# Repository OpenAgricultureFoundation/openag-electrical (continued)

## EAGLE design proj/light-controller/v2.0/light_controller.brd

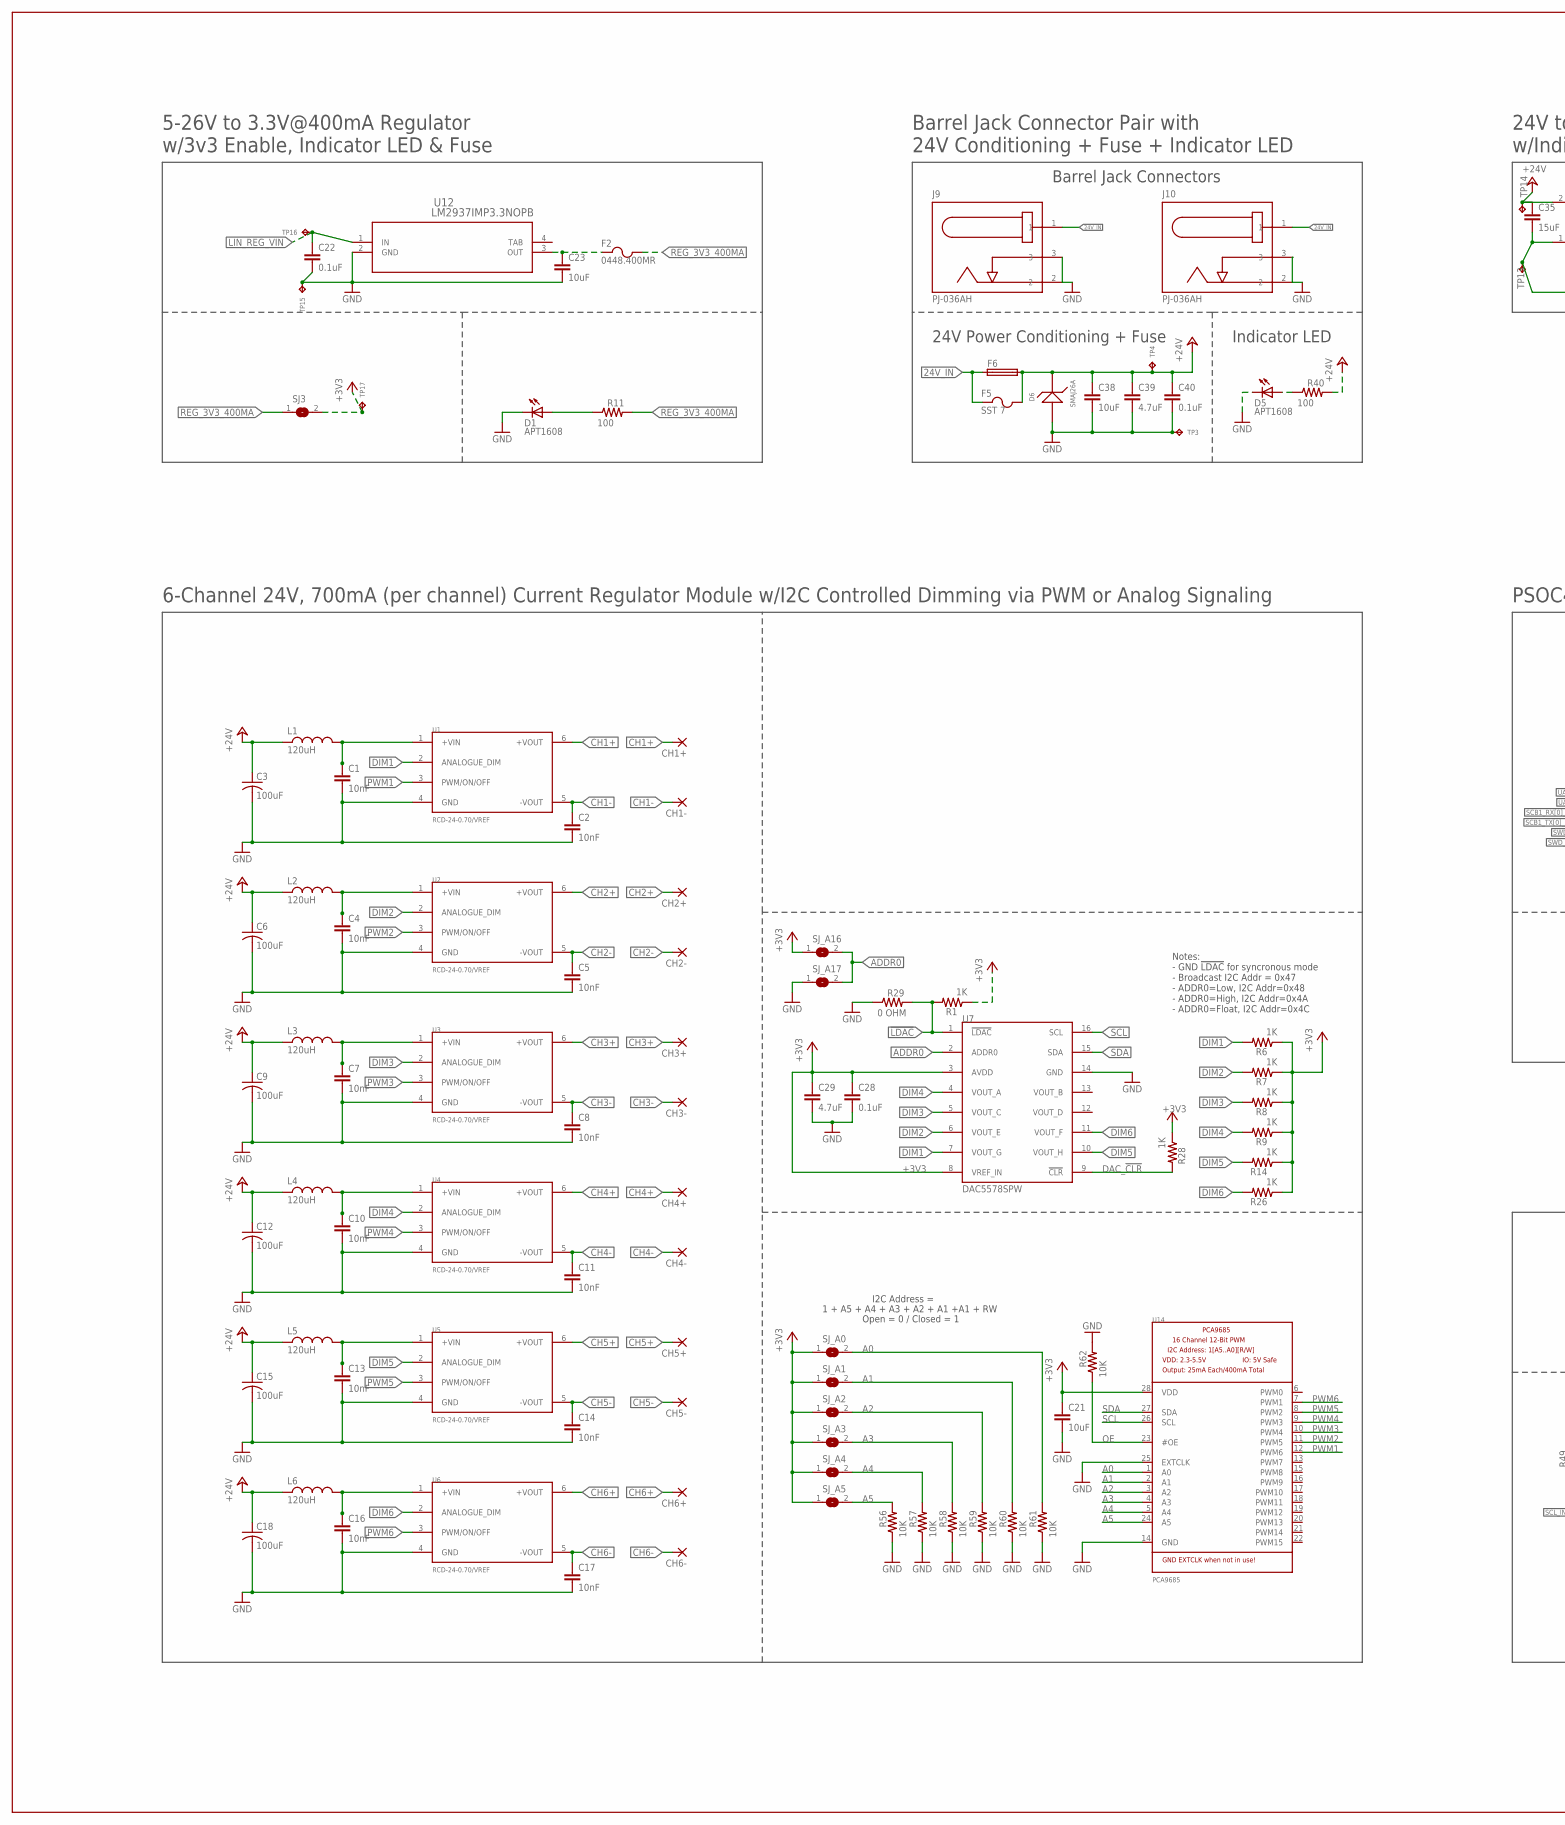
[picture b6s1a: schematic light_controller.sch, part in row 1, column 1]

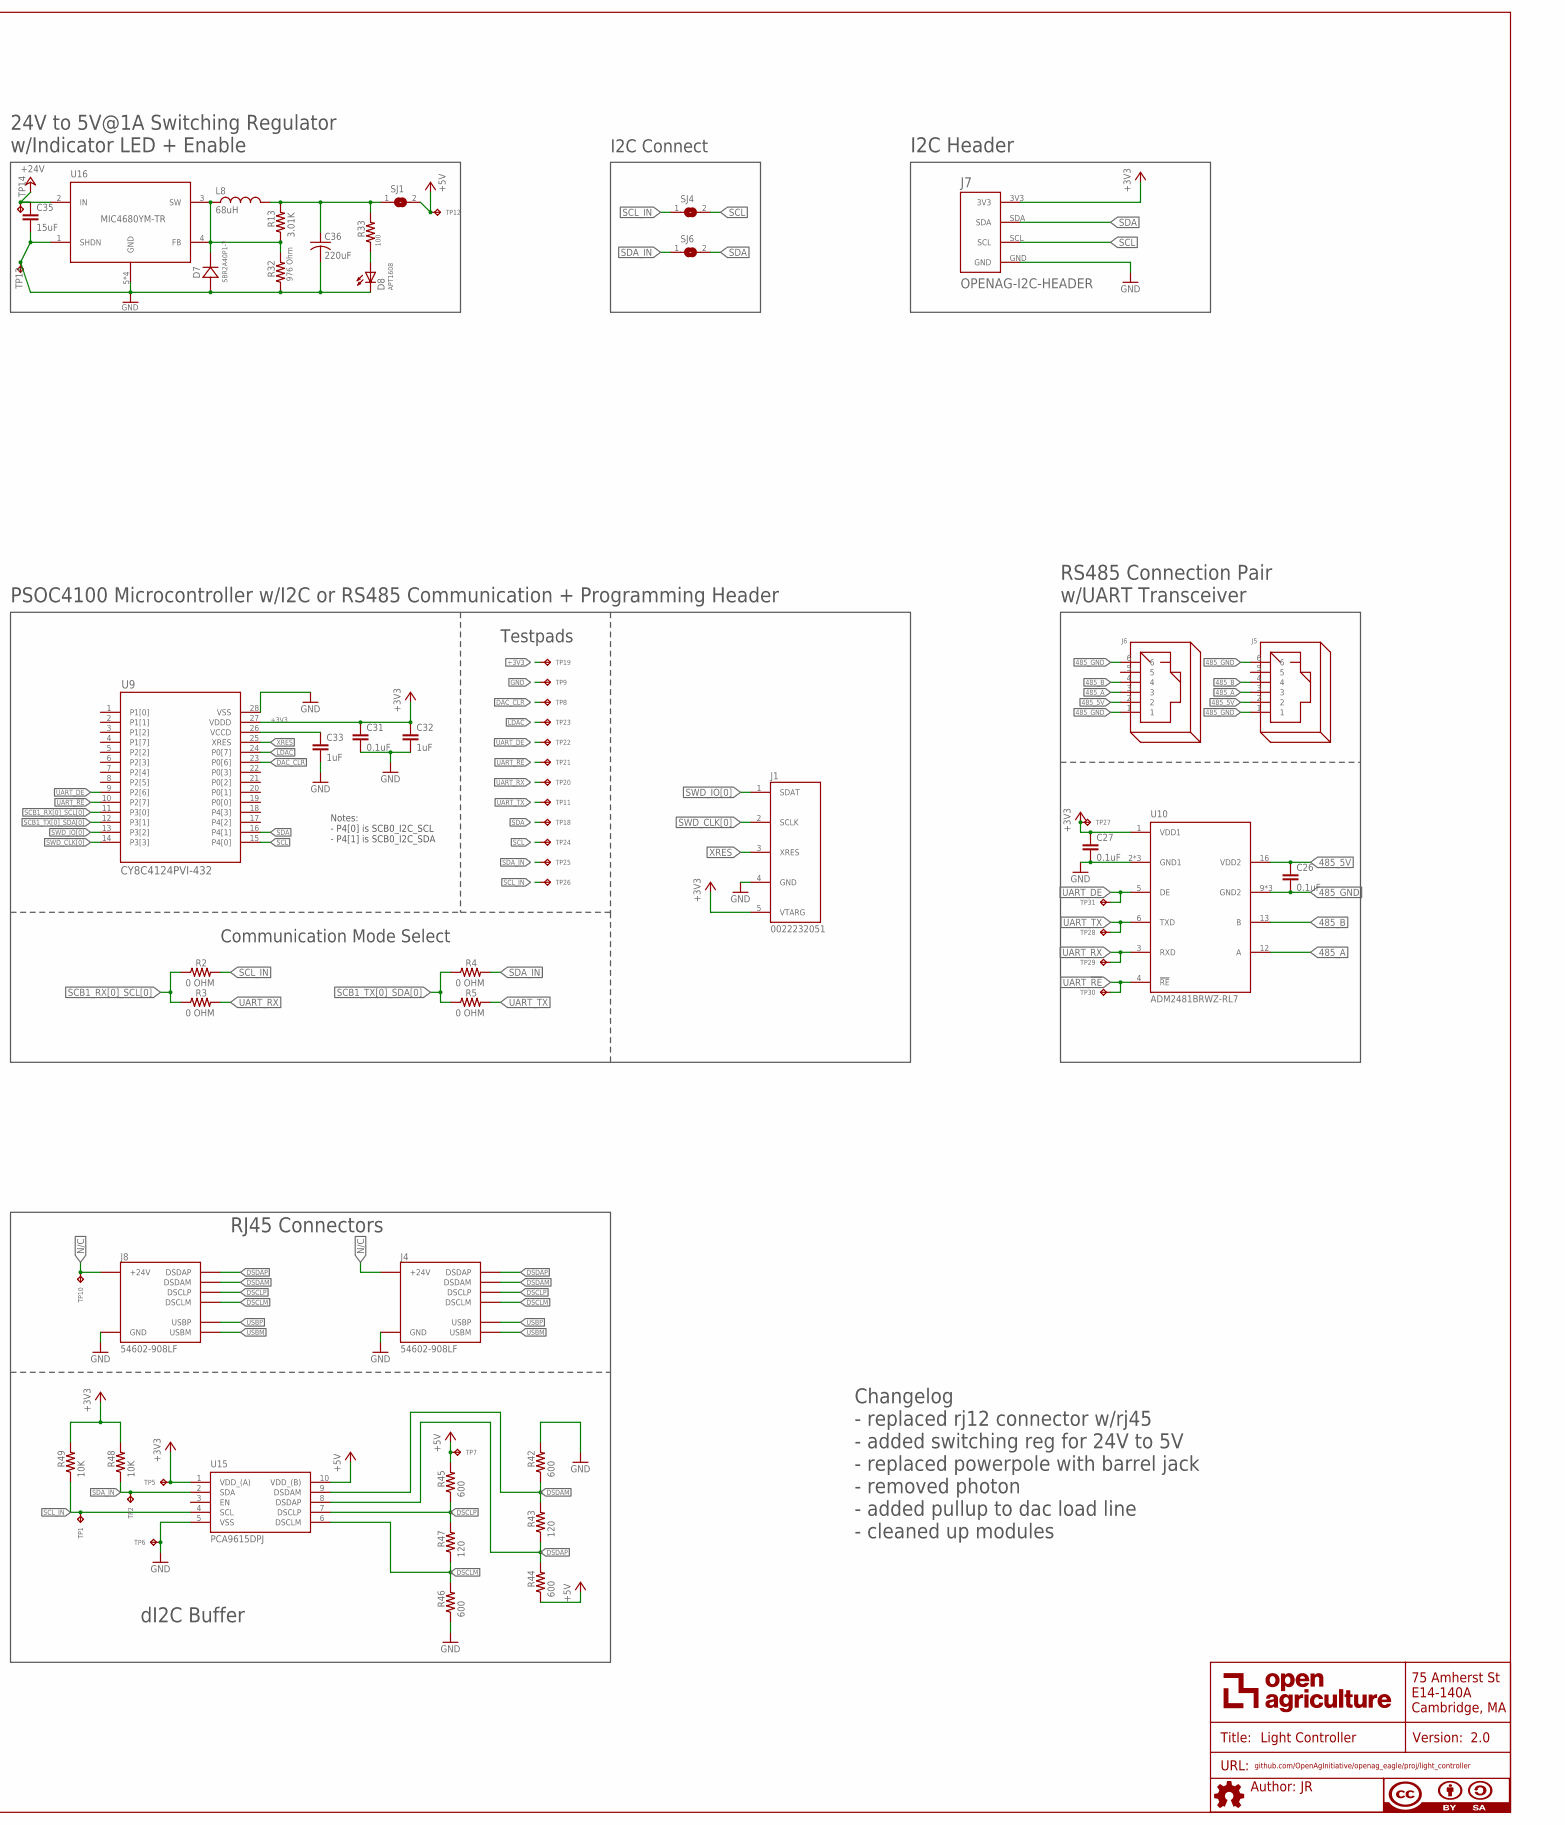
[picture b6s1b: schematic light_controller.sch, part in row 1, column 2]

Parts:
C1, C2, C4, C5, C7, C8, C10, C11, C13, C14, C16, C17: 10nF; C0603
C3, C6, C9, C12, C15, C18: 100uF; EEE-1HA101UP
C21, C23, C38: 10uF; C0805
C22, C26, C27, C28, C31, C40: 0.1uF; C0603
C29, C39: 4.7uF; C0805
C32, C33: 1uF; C0603
C35: 15uF; C0805
C36: 220uF; CT7343
CH1+, CH1-, CH2+, CH2-, CH3+, CH3-, CH4+, CH4-, CH5+, CH5-, CH6+, CH6-: 3,17/1,3
D1, D5, D8: APT1608; CHIPLED_0603
D6: SMAJ26A; SMA
D7: SBR2A40P1-7; POWERDI123
F2: 0448.400MR; 0603
F5: SST 7; SS
F6: GSH15
FRAME1: DOCFIELD
J1: 0022232051; 22-23-2051
J4, J8: 54602-908LF; OPENAG-V1-RJ45
J5, J6: OPENAG-RS485-RJ12
J7: OPENAG-I2C-HEADER
J9, J10: PJ-036AH
L1, L2, L3, L4, L5, L6: 120uH; 74404064121
L8: 68uH; UP2B
R1, R6, R7, R8, R9, R14, R26, R28: 1K; RC0603N
R2, R3, R4, R5, R29: 0 OHM; RC0603N
R11, R33, R40: 100; RC0603N
R13: 3.01K; RC0603N
R32: 976 Ohm; RC0603N
R42, R44, R45, R46: 600; RC0603N
R43, R47: 120; RC0603N
R48, R49, R56, R57, R58, R59, R60, R61, R62: 10K; RC0603N
SJ1, SJ3, SJ4, SJ6: SOLDERJUMPERREFLOW_NOPASTE; SOLDERJUMPER_REFLOW_NOPASTE
SJ_A0, SJ_A1, SJ_A2, SJ_A3, SJ_A4, SJ_A5, SJ_A16, SJ_A17: SOLDERJUMPERREFLOW_NOPASTE; SOLDERJUMPER_REFLOW_NOPASTE
TP1, TP2, TP3, TP4, TP5, TP6, TP7, TP10, TP12, TP13, TP14, TP15, TP16, TP17: TPTP06R; TP06R
TP8, TP9, TP11, TP18, TP19, TP20, TP21, TP22, TP23, TP24, TP25, TP26, TP27, TP28, TP29, TP30, TP31: TPTP04R; TP04R
U1, U2, U3, U4, U5, U6: RCD-24-0.70/VREF; RCD-24-PINNED
U7: DAC5578SPW; TSSOP16
U9: CY8C4124PVI-432; SSOP-28
U10: ADM2481BRWZ-RL7; SOIC16LWB
U12: LM2937IMP3.3NOPB; MP04A
U14: PCA9685; TSSOP28
U15: PCA9615DPJ; SOP50P490X110-10N
U16: MIC4680YM-TR; SOIC8

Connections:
24V_IN: F5.1, F6.1, J9.1, J10.1
485_5V: C26.1, J5.2, J6.2, U10.16 (VDD2)
485_A: J5.3, J6.3, U10.12 (A)
485_B: J5.4, J6.4, U10.13 (B)
485_GND: C26.2, J5.1, J5.6, J6.1, J6.6, U10.9 (GND2), U10.10 (GND2), U10.15 (GND2)
!LDAC!: R1.2, R29.2, TP23.1, U7.1 (!LDAC!), U9.24 (P0[7])
+3V3: C21.1, C27.1, C28.1, C29.1, C31.1, C32.1, J1.5 (VTARG), J7.3V3, R1.1, R6.1, R7.1, R8.1, R9.1, R14.1, R26.1, R28.1, R48.2, R49.2, SJ3.2, SJ_A0.1, SJ_A1.1, SJ_A2.1, SJ_A3.1, SJ_A4.1, SJ_A5.1, SJ_A16.1, TP5.TP, TP17.TP, TP19.1, TP27.1, U7.3 (AVDD), U7.8 (VREF_IN), U9.27 (VDDD), U10.1 (VDD1), U14.28 (VDD), U15.1 (VDD_(A))
+5V: R44.1, R45.2, SJ1.2, TP7.TP, TP12.TP, U15.10 (VDD_(B))
+24V: C3.+ (1(+)), C6.+ (1(+)), C9.+ (1(+)), C12.+ (1(+)), C15.+ (1(+)), C18.+ (1(+)), C35.1, C38.1, C39.1, C40.1, D6.1, F5.2, F6.2, L1.1, L2.1, L3.1, L4.1, L5.1, L6.1, R40.2, TP4.TP, TP14.TP, U16.2 (IN)
A0: R61.2, SJ_A0.2, U14.1 (A0)
A1: R60.2, SJ_A1.2, U14.2 (A1)
A2: R59.2, SJ_A2.2, U14.3 (A2)
A3: R58.2, SJ_A3.2, U14.4 (A3)
A4: R57.2, SJ_A4.2, U14.5 (A4)
A5: R56.2, SJ_A5.2, U14.24 (A5)
ADDR0: SJ_A16.2, SJ_A17.2, U7.2 (ADDR0)
CH1+: CH1+.1, U1.6 (+VOUT)
CH1-: C2.1, CH1-.1, U1.5 (-VOUT)
CH2+: CH2+.1, U2.6 (+VOUT)
CH2-: C5.1, CH2-.1, U2.5 (-VOUT)
CH3+: CH3+.1, U3.6 (+VOUT)
CH3-: C8.1, CH3-.1, U3.5 (-VOUT)
CH4+: CH4+.1, U4.6 (+VOUT)
CH4-: C11.1, CH4-.1, U4.5 (-VOUT)
CH5+: CH5+.1, U5.6 (+VOUT)
CH5-: C14.1, CH5-.1, U5.5 (-VOUT)
CH6+: CH6+.1, U6.6 (+VOUT)
CH6-: C17.1, CH6-.1, U6.5 (-VOUT)
DAC_!CLR!: R28.2, TP8.1, U7.9 (!CLR!), U9.23 (P0[6])
DIM1: R6.2, U1.2 (ANALOGUE_DIM), U7.7 (VOUT_G)
DIM2: R7.2, U2.2 (ANALOGUE_DIM), U7.6 (VOUT_E)
DIM3: R8.2, U3.2 (ANALOGUE_DIM), U7.5 (VOUT_C)
DIM4: R9.2, U4.2 (ANALOGUE_DIM), U7.4 (VOUT_A)
DIM5: R14.2, U5.2 (ANALOGUE_DIM), U7.10 (VOUT_H)
DIM6: R26.2, U6.2 (ANALOGUE_DIM), U7.11 (VOUT_F)
DSCLM: J4.DSCLM(5) (DSCLM), J8.DSCLM(5) (DSCLM), R46.2, R47.1, U15.6 (DSCLM)
DSCLP: J4.DSCLP(4) (DSCLP), J8.DSCLP(4) (DSCLP), R45.1, R47.2, U15.7 (DSCLP)
DSDAM: J4.DSDAM(2) (DSDAM), J8.DSDAM(2) (DSDAM), R42.1, R43.2, U15.9 (DSDAM)
DSDAP: J4.DSDAP(1) (DSDAP), J8.DSDAP(1) (DSDAP), R43.1, R44.2, U15.8 (DSDAP)
GND: C1.2, C2.2, C3.- (2(-)), C4.2, C5.2, C6.- (2(-)), C7.2, C8.2, C9.- (2(-)), C10.2, C11.2, C12.- (2(-)), C13.2, C14.2, C15.- (2(-)), C16.2, C17.2, C18.- (2(-)), C21.2, C22.2, C23.2, C27.2, C28.2, C29.2, C31.2, C32.2, C33.2, C35.2, C36.- (2(-)), C38.2, C39.2, C40.2, D1.C, D5.C, D6.2, D7.- (21), D8.C, J1.4 (GND), J4.GND(3) (GND), J7.GND, J8.GND(3) (GND), J9.2, J9.3, J10.2, J10.3, R29.1, R32.1, R42.2, R46.1, R56.1, R57.1, R58.1, R59.1, R60.1, R61.1, R62.2, SJ_A17.1, TP3.TP, TP6.TP, TP9.1, TP13.TP, TP15.TP, U1.4 (GND), U2.4 (GND), U3.4 (GND), U4.4 (GND), U5.4 (GND), U6.4 (GND), U7.14 (GND), U9.28 (VSS), U10.2 (GND1), U10.7 (GND1), U10.8 (GND1), U12.2 (GND), U14.14 (GND), U14.25 (EXTCLK), U15.5 (VSS), U16.1 (SHDN), U16.5 (GND), U16.6 (GND), U16.7 (GND), U16.8 (GND)
LIN_REG_VIN: C22.1, TP16.TP, U12.1 (IN)
unnamed: C1.1, L1.2, U1.1 (+VIN)
unnamed: C4.1, L2.2, U2.1 (+VIN)
unnamed: C7.1, L3.2, U3.1 (+VIN)
unnamed: C10.1, L4.2, U4.1 (+VIN)
unnamed: C13.1, L5.2, U5.1 (+VIN)
unnamed: C16.1, L6.2, U6.1 (+VIN)
unnamed: D1.A, R11.1
unnamed: D7.+ (12), L8.1, R13.1, R32.2, U16.3 (SW), U16.4 (FB)
unnamed: C23.1, F2.1, U12.3 (OUT)
unnamed: D8.A, R33.1
unnamed: C33.1, U9.26 (VCCD)
unnamed: C36.+ (1(+)), L8.2, R13.2, R33.2, SJ1.1
unnamed: D5.A, R40.1
N/C: J4.24V(6) (+24V), J8.24V(6) (+24V), TP10.TP
OE: R62.1, U14.23 (#OE)
PWM1: U1.3 (PWM/ON/OFF), U14.12 (PWM6)
PWM2: U2.3 (PWM/ON/OFF), U14.11 (PWM5)
PWM3: U3.3 (PWM/ON/OFF), U14.10 (PWM4)
PWM4: U4.3 (PWM/ON/OFF), U14.9 (PWM3)
PWM5: U5.3 (PWM/ON/OFF), U14.8 (PWM2)
PWM6: U6.3 (PWM/ON/OFF), U14.7 (PWM1)
REG_3V3_400MA: F2.2, R11.2, SJ3.1
SCB1_RX[0]_SCL[0]: R2.1, R3.1, U9.11 (P3[0])
SCB1_TX[0]_SDA[0]: R4.1, R5.1, U9.12 (P3[1])
SCL: J7.SCL, SJ4.2, TP24.1, U7.16 (SCL), U9.15 (P4[0]), U14.26 (SCL)
SCL_IN: R2.2, R49.1, SJ4.1, TP1.TP, TP26.1, U15.4 (SCL)
SDA: J7.SDA, SJ6.2, TP18.1, U7.15 (SDA), U9.16 (P4[1]), U14.27 (SDA)
SDA_IN: R4.2, R48.1, SJ6.1, TP2.TP, TP25.1, U15.2 (SDA)
SWD_CLK[0]: J1.2 (SCLK), U9.14 (P3[3])
SWD_IO[0]: J1.1 (SDAT), U9.13 (P3[2])
TAB: U12.4 (TAB)
UART_!RE!: TP21.1, TP30.1, U9.10 (P2[7]), U10.4 (!RE!)
UART_DE: TP22.1, TP31.1, U9.9 (P2[6]), U10.5 (DE)
UART_RX: R3.2, TP20.1, TP29.1, U10.3 (RXD)
UART_TX: R5.2, TP11.1, TP28.1, U10.6 (TXD)
USBM: J4.USBM(8) (USBM), J8.USBM(8) (USBM)
USBP: J4.USBP(7) (USBP), J8.USBP(7) (USBP)
XRES: J1.3 (XRES), U9.25 (XRES)

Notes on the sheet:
Notes: - GND !LDAC! for syncronous mode - Broadcast I2C Addr = 0x47 - ADDR0=Low, I2C Addr=0x48 - ADDR0=High, I2C Addr=0x4A - ADDR0=Float, I2C Addr=0x4C
1 + A5 + A4 + A3 + A2 + A1 +A1 + RW
I2C Address =
Open = 0 / Closed = 1
RS485 Connection Pair w/UART Transceiver
PSOC4100 Microcontroller w/I2C or RS485 Communication + Programming Header
I2C Header
6-Channel 24V, 700mA (per channel) Current Regulator Module w/I2C Controlled Dimming via PWM or Analog Signaling
Changelog - replaced rj12 connector w/rj45 - added switching reg for 24V to 5V - replaced powerpole with barrel jack - removed photon - added pullup to dac load line - cleaned up modules
Barrel Jack Connectors
Barrel Jack Connector Pair with 24V Conditioning + Fuse + Indicator LED
24V Power Conditioning + Fuse
Indicator LED
dI2C Buffer
RJ45 Connectors
24V to 5V@1A Switching Regulator w/Indicator LED + Enable
5-26V to 3.3V@400mA Regulator w/3v3 Enable, Indicator LED & Fuse
Notes: - P4[0] is SCB0_I2C_SCL - P4[1] is SCB0_I2C_SDA
Communication Mode Select
I2C Connect
Testpads

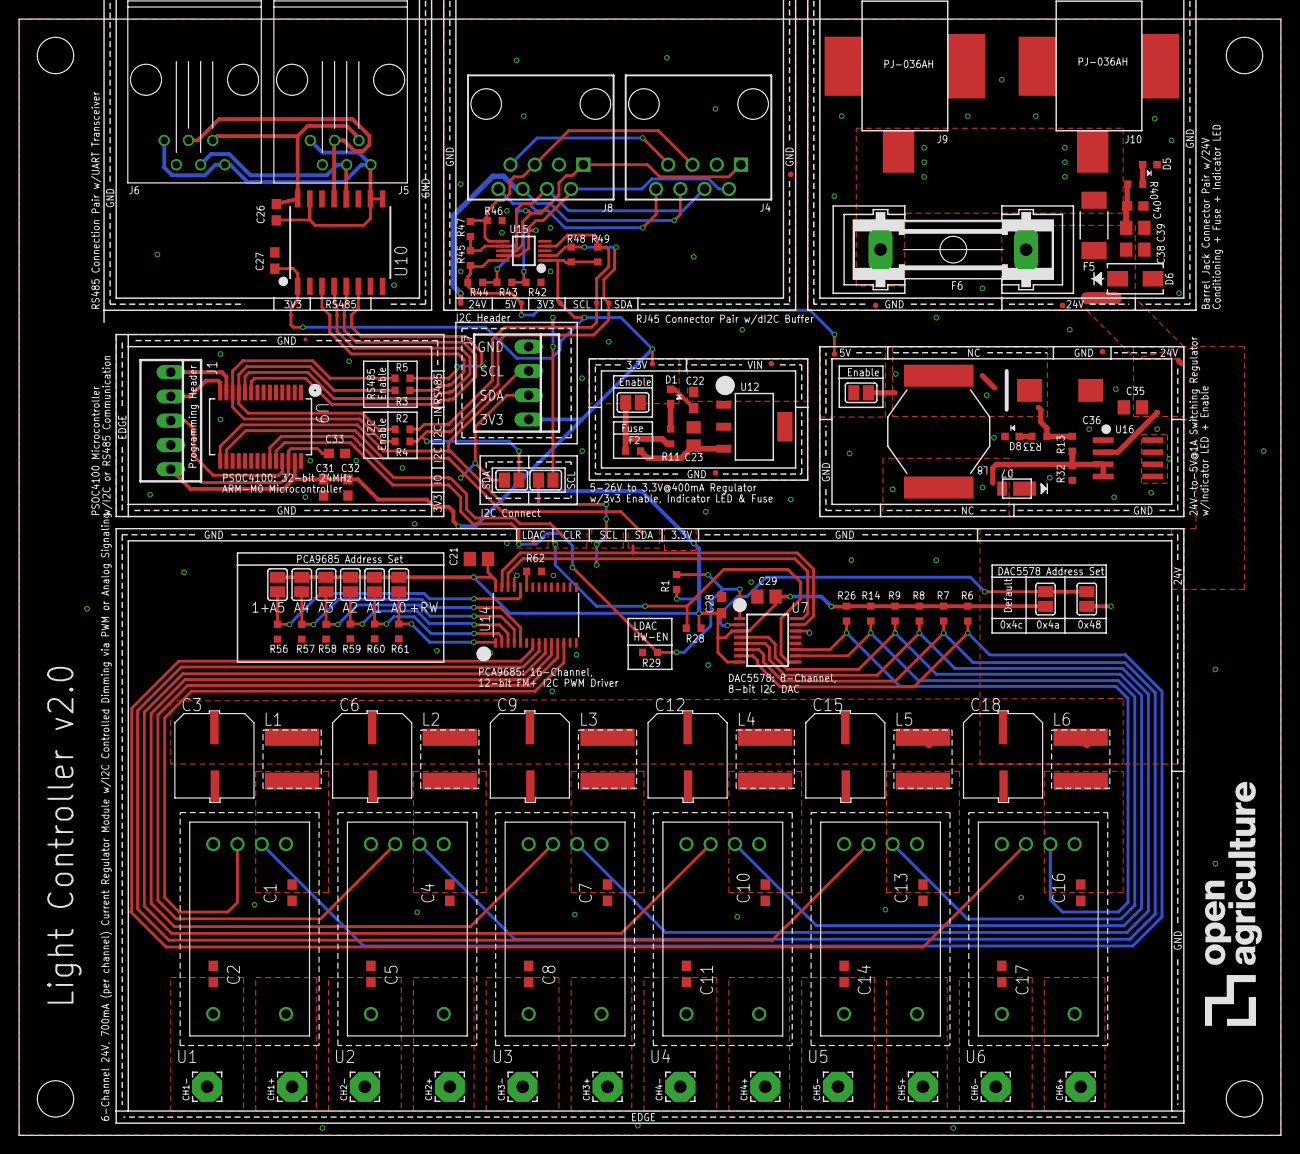
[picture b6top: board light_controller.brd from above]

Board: 2 copper layers, 132.1 x 116.8 mm, 163 parts (1 on the bottom side), 78 nets.

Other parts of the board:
U$1, U$2, U$3, U$4: OPENAG-CORNER-MOUNTING-HOLE
U$5: OPENAG-LOGO-1000-MIL

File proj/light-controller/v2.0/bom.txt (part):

Partlist exported from /home/jake/projects/openag_eagle/proj/light-controller/v2.0/light_controller.sch at 2/12/18 3:31 PM

Qty Value             Device                           Package                     Parts                                                                                              Description                                                                     
12                    3,17/1,3                         3,17/1,3                    CH1+, CH1-, CH2+, CH2-, CH3+, CH3-, CH4+, CH4-, CH5+, CH5-, CH6+, CH6-                             THROUGH-HOLE PAD                                                                
1                     DOCFIELD                         DOCFIELD                    FRAME1                                                                                             DOCUMENT FIELD                                                                  
1                     GSH15                            GSH15                       F6                                                                                                 FUSE HOLDER                                                                     
12                    SOLDERJUMPERREFLOW_NOPASTE       SOLDERJUMPER_REFLOW_NOPASTE SJ1, SJ3, SJ4, SJ6, SJ_A0, SJ_A1, SJ_A2, SJ_A3, SJ_A4, SJ_A5, SJ_A16, SJ_A17                       SMD Solder JUMPER                                                               
5   0 OHM             0OHM-RC0603JR-070RL              RC0603N                     R2, R3, R4, R5, R29                                                                                Yageo - RC0603JR-070RL - RES SMD 0 OHM JUMPER 1/10W 0603                        
6   0.1uF             0.1UF-C0603C104K5RACTU           C0603                       C22, C26, C27, C28, C31, C40                                                                       Kemet - C0603C104K5RACTU - CAP CER 0.1UF 50V X7R 0603                           
1   0022232051        MINI-PROG3-5POS-MATING-CONNECTOR 22-23-2051                  J1                                                                                                 Molex - 0022232051 - CONN HEADER 5POS .100 VERT TIN                             
1   0448.400MR        0438.375WR                       0603                        F2                                                                                                 Littelfuse Inc. - 0448.400MR - FUSE BOARD MNT 400MA 125VAC/VDC                  
3   100               100OHM-RC0603JR-07100RL          RC0603N                     R11, R33, R40                                                                                      Yageo - RC0603JR-07100RL - RES SMD 100 OHM 5% 1/10W 0603                        
6   100uF             100UF-EEE-1HA101UP               EEE-1HA101UP                C3, C6, C9, C12, C15, C18                                                                          Panasonic - EEE-1HA101UP - ELECTROLYTIC CAP ALUM 100UF 20% 50V SMD              
9   10K               10K-ERJ-3EKF1002V                RC0603N                     R48, R49, R56, R57, R58, R59, R60, R61, R62                                                        Panasonic - ERJ-3EKF1002V - RES SMD 10K OHM 1% 1/10W 0603                       
12  10nF              10NF-C0603C103K5RACTU            C0603                       C1, C2, C4, C5, C7, C8, C10, C11, C13, C14, C16, C17                                               KEMET - C0603C103K5RACTU - CAP CER 10000PF 50V X7R 0603                         
3   10uF              10UF-GMK212BBJ106KG-T            C0805                       C21, C23, C38                                                                                      Taiyo Yuden - GMK212BBJ106KG-T - CAP CER 10UF 35V X5R 0805                      
2   120               120OHM-RC0603FR-07120RL          RC0603N                     R43, R47                                                                                           Yageo - RC0603FR-07120RL - RES SMD 120 OHM 1% 1/10W 0603                        
6   120uH             120UH-74404064121                74404064121                 L1, L2, L3, L4, L5, L6                                                                             Wurth Electronics - 74404064121 - FIXED IND 120UH 790MA 520 MOHM                
1   15uF              15UF-C2012X5R1V156M125AC         C0805                       C35                                                                                                TDK Corporation - C2012X5R1V156M125AC - CAP CER 15UF 35V X5R 0805               
8   1K                1K-ERJ-PB3D1001V                 RC0603N                     R1, R6, R7, R8, R9, R14, R26, R28                                                                  Panasonic - P20283CT-ND - RES SMD 1K OHM 0.5% 1/5W 0603                         
2   1uF               1UF-CL10A105KB8NNNC              C0603                       C32, C33                                                                                           Samsung - CL10A105KB8NNNC - CAP CER 1UF 50V X5R 0603                            
1   220uF             220UF-TPSY227K010R0100           CT7343                      C36                                                                                                AVX Corporation - TPSY227K010R0100 - CAP TANT 220UF 10V 10% 2917                
1   3.01K             3.01K-RC0603FR-073K01L           RC0603N                     R13                                                                                                Yageo - RC0603FR-073K01L - RES SMD 3.01K OHM 1% 1/10W 0603                      
2   4.7uF             4.7UF-CL21A475KBQNNNE            C0805                       C29, C39                                                                                           Samsung - CL21A475KBQNNNE - CAP CER 4.7UF 50V X5R 0805                          
2   54602-908LF       OPENAG-V1-RJ45PTH                OPENAG-V1-RJ45              J4, J8                                                                                             Amphenol FCI - 54602-908LF - CONN MOD JACK 8P8C R/A UNSHLD                      
4   600               600OHM-RC0603FR-07604RL          RC0603N                     R42, R44, R45, R46                                                                                 Yageo - RC0603FR-07604RL - RES SMD 604 OHM 1% 1/10W 0603                        
1   68uH              68UH-UP2B-680-R                  UP2B                        L8                                                                                                 Eaton - UP2B-680-R - FIXED IND 68UH 1.5A 178.7 MOHM                             
1   976 Ohm           982OHM-RC0603FR-07976RL          RC0603N                     R32                                                                                                Yageo - RC0603FR-07976RL - RES SMD 976 OHM 1% 1/10W 0603                        
1   ADM2481BRWZ-RL7   ADM2481BRWZ-RL7                  SOIC16LWB                   U10                                                                                                Analog Devices - ADM2481BRWZ-RL7 - DGTL ISO RS422/RS485 16SOIC                  
3   APT1608           APT1608CGCK                      CHIPLED_0603                D1, D5, D8                                                                                         Kingbright - APT1608CGCK - LED GREEN CLEAR 0603 SMD                             
1   CY8C4124PVI-432   CY8C4124PVI-432                  SSOP-28                     U9                                                                                                 Cypress - CY8C4124PVI-432 - IC MCU 32BIT 16KB FLASH 28SSOP                      
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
